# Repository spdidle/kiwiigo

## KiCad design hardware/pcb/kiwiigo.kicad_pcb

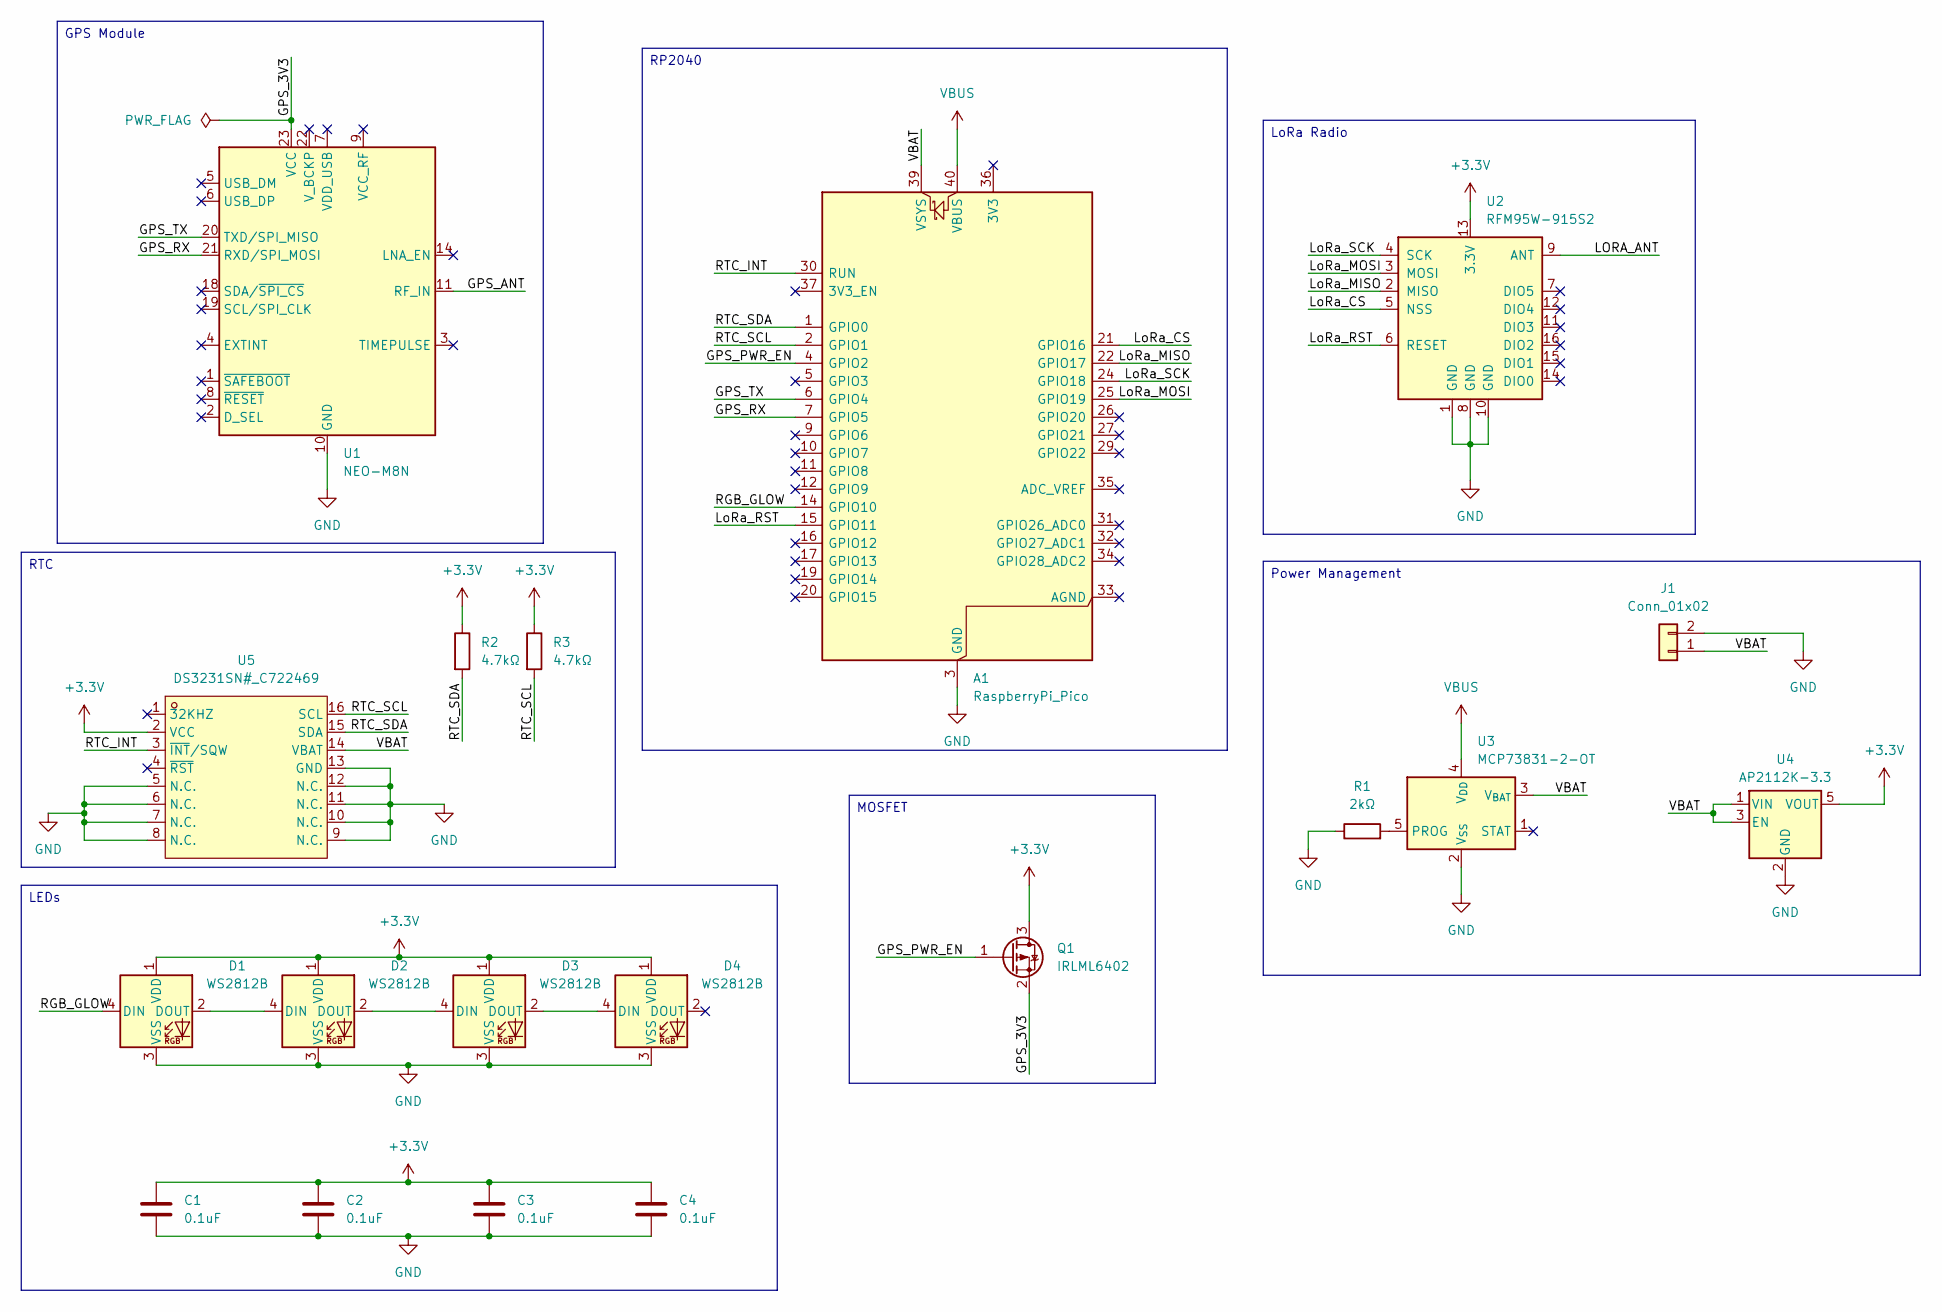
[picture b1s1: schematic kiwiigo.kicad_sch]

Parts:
A1: RaspberryPi_Pico; RaspberryPi_Pico_SMD_HandSolder
C1, C2, C3, C4: 0.1uF; C_0805_2012Metric_Pad1.18x1.45mm_HandSolder
D1, D2, D3, D4: WS2812B; LED_WS2812B_PLCC4_5.0x5.0mm_P3.2mm
J1: Conn_01x02; JST_PH_B2B-PH-K_1x02_P2.00mm_Vertical
Q1: IRLML6402; SOT-23
R1: 2kΩ; R_0805_2012Metric_Pad1.20x1.40mm_HandSolder
R2, R3: 4.7kΩ; R_0805_2012Metric_Pad1.20x1.40mm_HandSolder
U1: NEO-M8N; GPSM-SMD_NEO-M8N
U2: RFM95W-915S2; HOPERF_RFM9XW_SMD
U3: MCP73831-2-OT; SOT-23-5
U4: AP2112K-3.3; SOT-23-5
U5: DS3231SN#_C722469; SOIC-16_L10.3-W7.5-P1.27-LS10.3-BL; MPN DS3231SN#; LCSC Part C722469

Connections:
+3.3V: C1.1, C2.1, C3.1, C4.1, D1.1 (VDD), D2.1 (VDD), D3.1 (VDD), D4.1 (VDD), Q1.3 (D), R2.1, R3.1, U2.13 (3.3V), U4.5 (VOUT), U5.2 (VCC)
/GPS_3V3: Q1.2 (S), U1.23 (VCC)
/GPS_ANT: U1.11 (RF_IN)
/GPS_PWR_EN: A1.4 (GPIO2), Q1.1 (G)
/GPS_RX: A1.7 (GPIO5), U1.21 (RXD/SPI_MOSI)
/GPS_TX: A1.6 (GPIO4), U1.20 (TXD/SPI_MISO)
/LORA_ANT: U2.9 (ANT)
/LoRa_CS: A1.21 (GPIO16), U2.5 (NSS)
/LoRa_MISO: A1.22 (GPIO17), U2.2 (MISO)
/LoRa_MOSI: A1.25 (GPIO19), U2.3 (MOSI)
/LoRa_RST: A1.15 (GPIO11), U2.6 (RESET)
/LoRa_SCK: A1.24 (GPIO18), U2.4 (SCK)
/RGB_GLOW: A1.14 (GPIO10), D1.4 (DIN)
/RTC_INT: A1.30 (RUN), U5.3 (~INT/SQW)
/RTC_SCL: A1.2 (GPIO1), R3.2, U5.16 (SCL)
/RTC_SDA: A1.1 (GPIO0), R2.2, U5.15 (SDA)
/VBAT: A1.39 (VSYS), J1.1, U3.3 (V_{BAT}), U4.1 (VIN), U4.3 (EN), U5.14 (VBAT)
GND: A1.3 (GND), A1.8 (GND), A1.13 (GND), A1.18 (GND), A1.23 (GND), A1.28 (GND), A1.38 (GND), C1.2, C2.2, C3.2, C4.2, D1.3 (VSS), D2.3 (VSS), D3.3 (VSS), D4.3 (VSS), J1.2, R1.1, U1.10 (GND), U1.12 (GND), U1.13 (GND), U1.24 (GND), U2.1 (GND), U2.8 (GND), U2.10 (GND), U3.2 (V_{SS}), U4.2 (GND), U5.5 (N.C.), U5.6 (N.C.), U5.7 (N.C.), U5.8 (N.C.), U5.9 (N.C.), U5.10 (N.C.), U5.11 (N.C.), U5.12 (N.C.), U5.13 (GND)
unnamed: D1.2 (DOUT), D2.4 (DIN)
unnamed: D2.2 (DOUT), D3.4 (DIN)
unnamed: D3.2 (DOUT), D4.4 (DIN)
unnamed: R1.2, U3.5 (PROG)
VBUS: A1.40 (VBUS), U3.4 (V_{DD})

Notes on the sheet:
MOSFET
RTC
LEDs
Power Management
LoRa Radio
GPS Module
RP2040

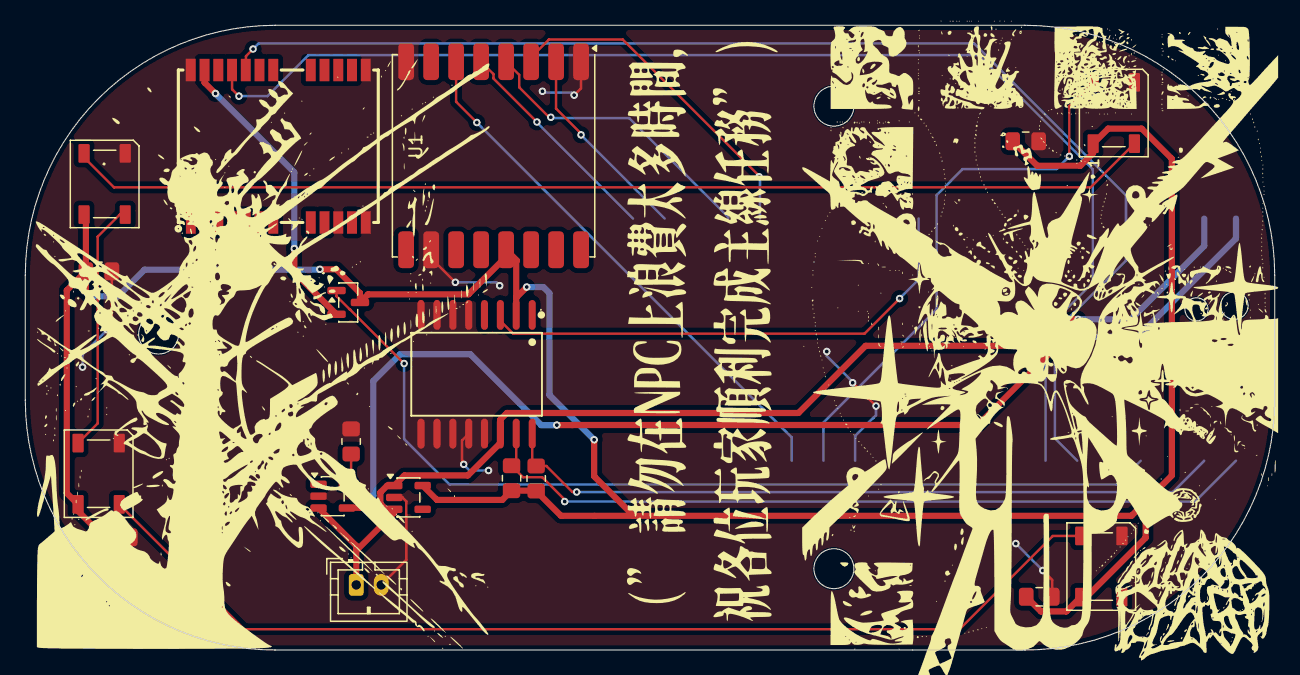
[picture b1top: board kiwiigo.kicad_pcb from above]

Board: 2 copper layers, 100.0 x 50.0 mm, 19 parts (1 on the bottom side), 21 nets.

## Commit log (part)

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2026-06-27 organizing files
    pcb and schematic both done
2026-06-27 delete kiwiigo folder
    why is old folder still here :'(
2026-06-27 gitignore
    gittyignoe
2026-06-27 Add .DS_Store to .gitignore
2026-06-27 chore: remove tracked .DS_Store
2026-06-27 STUPID ds store whyisnt it ignoring walaoo
2026-06-27 Restore folders/files and update gitignore
2026-06-27 help
2026-06-27 add placeholder
    placeholder so it will show up on github </3
2026-06-27 Case done 😁👍👍👌
    mi el finisho case 👌 #fairs #green
